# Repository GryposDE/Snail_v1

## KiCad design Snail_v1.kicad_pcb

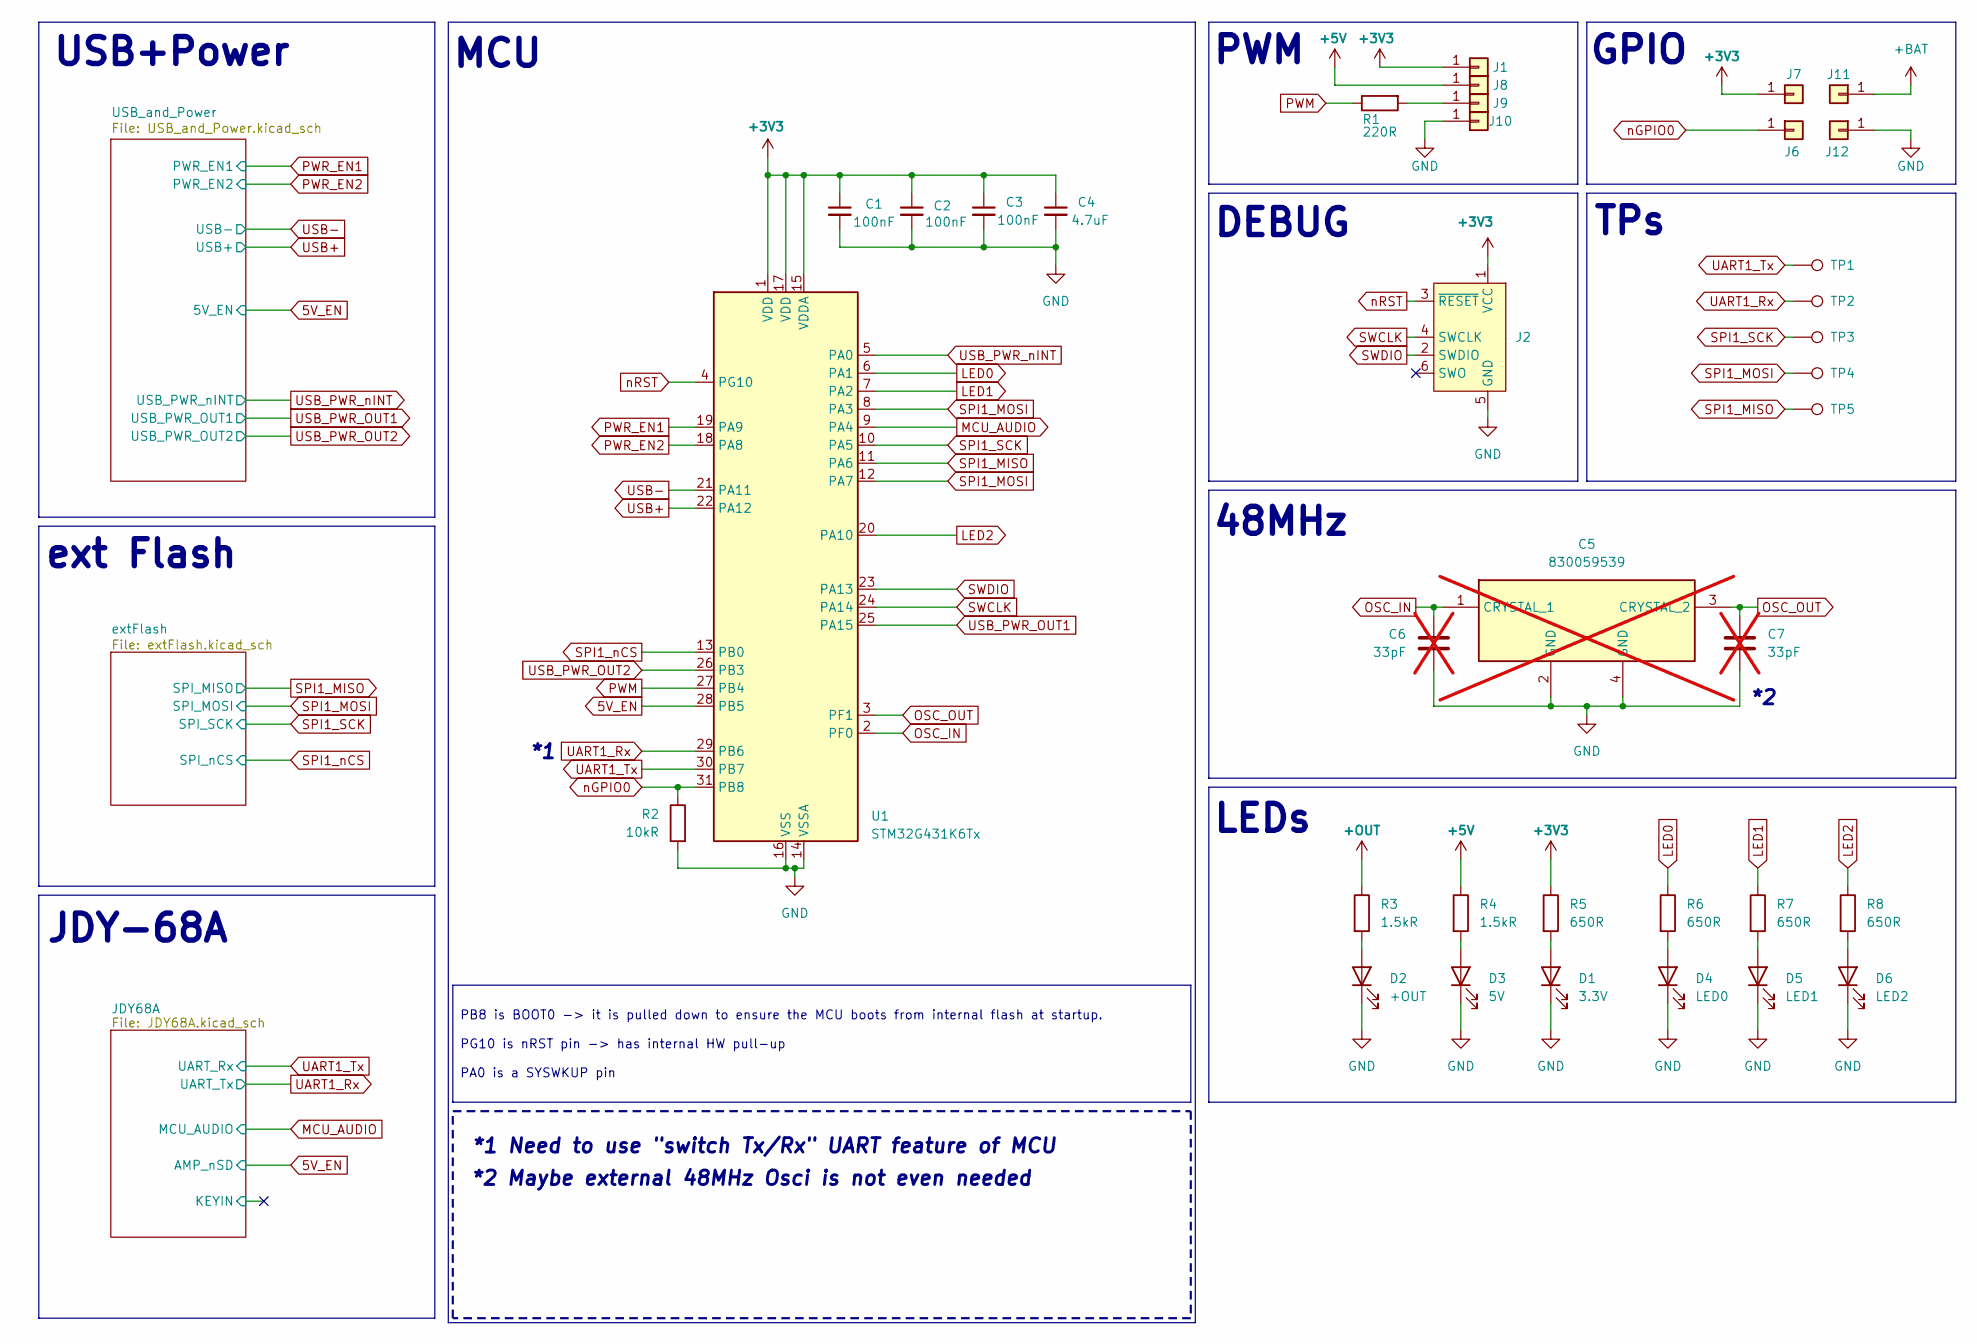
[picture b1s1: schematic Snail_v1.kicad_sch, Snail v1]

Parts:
C1, C2, C3: 100nF; C_0805_2012Metric_Pad1.18x1.45mm_HandSolder
C4: 4.7uF; C_0805_2012Metric_Pad1.18x1.45mm_HandSolder
C5: 830059539; Mouser Part Number 710-830059539; not fitted
C6, C7: 33pF; C_0805_2012Metric_Pad1.18x1.45mm_HandSolder; not fitted
D1: 3.3V; LED_0805_2012Metric_Pad1.15x1.40mm_HandSolder
D2: +OUT; LED_0805_2012Metric_Pad1.15x1.40mm_HandSolder
D3: 5V; LED_0805_2012Metric_Pad1.15x1.40mm_HandSolder
D4: LED0; LED_0805_2012Metric_Pad1.15x1.40mm_HandSolder
D5: LED1; LED_0805_2012Metric_Pad1.15x1.40mm_HandSolder
D6: LED2; LED_0805_2012Metric_Pad1.15x1.40mm_HandSolder
J1, J6, J7, J8, J9, J10, J11, J12: Conn_01x01; SolderWirePad_1x01_SMD_1.5x3mm
J2: Conn_ARM_SWD_TagConnect_TC2030-NL; Tag-Connect_TC2030-IDC-NL_2x03_P1.27mm_Vertical
R1: 220R; R_0805_2012Metric_Pad1.20x1.40mm_HandSolder
R2: 10kR; R_0805_2012Metric_Pad1.20x1.40mm_HandSolder
R3, R4: 1.5kR; R_0805_2012Metric_Pad1.20x1.40mm_HandSolder
R5, R6, R7, R8: 650R; R_0805_2012Metric_Pad1.20x1.40mm_HandSolder
TP1, TP2, TP3, TP4, TP5: TestPoint; TestPoint_Pad_D1.0mm
U1: STM32G431K6Tx; LQFP-32_7x7mm_P0.8mm

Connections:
5V_EN: U1.28 (PB5); also elsewhere on the board
+3V3: C1.1, C2.1, C3.1, C4.1, J1.1, J2.1 (VCC), J7.1, R5.1, U1.1 (VDD), U1.15 (VDDA), U1.17 (VDD); also elsewhere on the board
+5V: J8.1, R4.1; also elsewhere on the board
+OUT: R3.1; also elsewhere on the board
GND: C1.2, C2.2, C3.2, C4.2, C5.2 (GND), C5.4 (GND), C6.2, C7.2, D1.1 (K), D2.1 (K), D3.1 (K), D4.1 (K), D5.1 (K), D6.1 (K), J2.5 (GND), J10.1, J12.1, R2.2, U1.14 (VSSA), U1.16 (VSS), U1.32 (VSS); also elsewhere on the board
LED0: R6.1, U1.6 (PA1)
LED1: R7.1, U1.7 (PA2)
LED2: R8.1, U1.20 (PA10)
MCU_AUDIO: U1.9 (PA4); also elsewhere on the board
unnamed: D1.2 (A), R5.2
unnamed: D2.2 (A), R3.2
unnamed: D3.2 (A), R4.2
unnamed: D4.2 (A), R6.2
unnamed: D5.2 (A), R7.2
unnamed: D6.2 (A), R8.2
unnamed: J9.1, R1.2
OSC_IN: C5.1 (CRYSTAL_1), C6.1, U1.2 (PF0)
OSC_OUT: C5.3 (CRYSTAL_2), C7.1, U1.3 (PF1)
PWM: R1.1, U1.27 (PB4)
PWR_EN1: U1.19 (PA9); also elsewhere on the board
PWR_EN2: U1.18 (PA8); also elsewhere on the board
SPI1_MISO: TP5.1, U1.11 (PA6); also elsewhere on the board
SPI1_MOSI: TP4.1, U1.8 (PA3), U1.12 (PA7); also elsewhere on the board
SPI1_SCK: TP3.1, U1.10 (PA5); also elsewhere on the board
SPI1_nCS: U1.13 (PB0); also elsewhere on the board
SWCLK: J2.4 (SWCLK), U1.24 (PA14)
SWDIO: J2.2 (SWDIO), U1.23 (PA13)
UART1_Rx: TP2.1, U1.29 (PB6); also elsewhere on the board
UART1_Tx: TP1.1, U1.30 (PB7); also elsewhere on the board
USB+: U1.22 (PA12); also elsewhere on the board
USB-: U1.21 (PA11); also elsewhere on the board
USB_PWR_OUT1: U1.25 (PA15); also elsewhere on the board
USB_PWR_OUT2: U1.26 (PB3); also elsewhere on the board
USB_PWR_nINT: U1.5 (PA0); also elsewhere on the board
nGPIO0: J6.1, R2.1, U1.31 (PB8); also elsewhere on the board
nRST: J2.3 (~RESET), U1.4 (PG10)

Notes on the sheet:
*2 Maybe external 48MHz Osci is not even needed
ext Flash
USB+Power
DEBUG
TPs
LEDs
JDY-68A
*1 Need to use "switch Tx/Rx" UART feature of MCU
MCU
PWM
GPIO
48MHz
PB8 is BOOT0 -> it is pulled down to ensure the MCU boots from internal flash at startup. PG10 is nRST pin -> has internal HW pull-up PA0 is a SYSWKUP pin

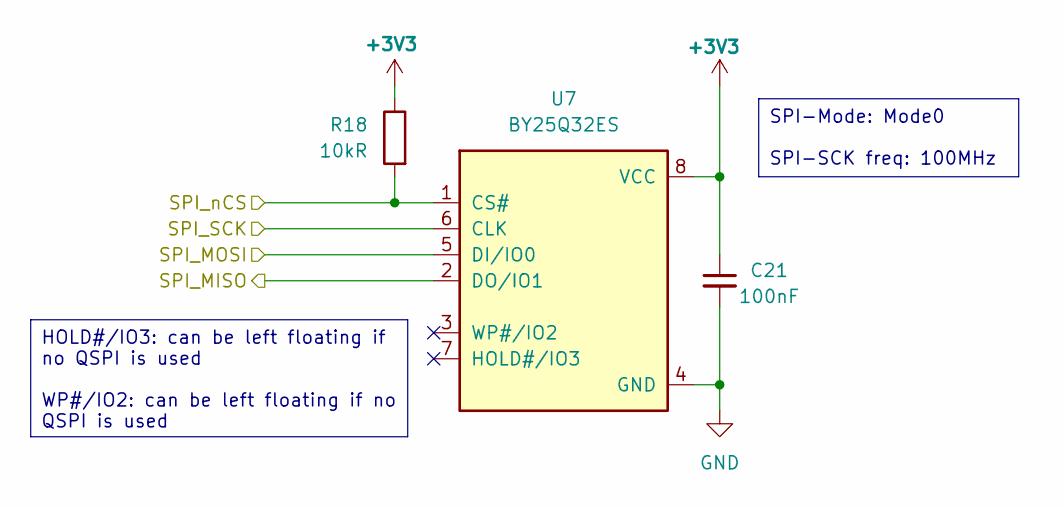
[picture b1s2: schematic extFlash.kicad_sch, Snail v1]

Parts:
C21: 100nF; C_0805_2012Metric_Pad1.18x1.45mm_HandSolder
R18: 10kR; R_0805_2012Metric_Pad1.20x1.40mm_HandSolder
U7: BY25Q32ES; BY25Q32ESSIG_SOIC-8_208mil

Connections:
+3V3: C21.1, R18.1, U7.8 (VCC); also elsewhere on the board
GND: C21.2, U7.4 (GND); also elsewhere on the board
SPI1_MISO: U7.2 (DO/IO1); also elsewhere on the board
SPI1_MOSI: U7.5 (DI/IO0); also elsewhere on the board
SPI1_SCK: U7.6 (CLK); also elsewhere on the board
SPI1_nCS: R18.2, U7.1 (CS#); also elsewhere on the board

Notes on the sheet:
SPI-Mode: Mode0 SPI-SCK freq: 100MHz
HOLD#/IO3: can be left floating if no QSPI is used WP#/IO2: can be left floating if no QSPI is used

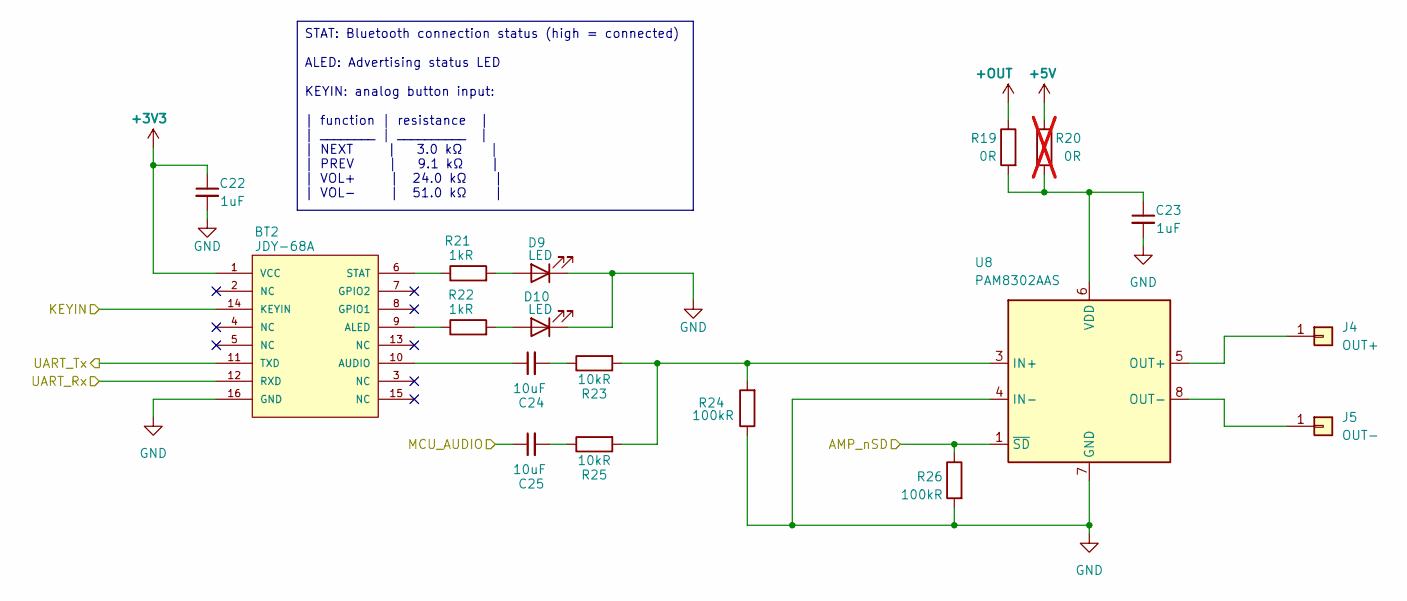
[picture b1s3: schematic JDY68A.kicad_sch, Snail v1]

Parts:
BT2: JDY-68A; JDY-68A_Module
C22, C23: 1uF; C_0805_2012Metric_Pad1.18x1.45mm_HandSolder
C24, C25: 10uF; C_0805_2012Metric_Pad1.18x1.45mm_HandSolder
D9, D10: LED; LED_0805_2012Metric_Pad1.15x1.40mm_HandSolder
J4: OUT+; SolderWirePad_1x01_SMD_1.5x3mm
J5: OUT-; SolderWirePad_1x01_SMD_1.5x3mm
R19: 0R; R_0805_2012Metric_Pad1.20x1.40mm_HandSolder
R20: 0R; R_0805_2012Metric_Pad1.20x1.40mm_HandSolder; not fitted
R21, R22: 1kR; R_0805_2012Metric_Pad1.20x1.40mm_HandSolder
R23, R25: 10kR; R_0805_2012Metric_Pad1.20x1.40mm_HandSolder
R24, R26: 100kR; R_0805_2012Metric_Pad1.20x1.40mm_HandSolder
U8: PAM8302AAS; MSOP-8_3x3mm_P0.65mm

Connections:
5V_EN: R26.1, U8.1 (~SD); also elsewhere on the board
+3V3: BT2.1 (VCC), C22.1; also elsewhere on the board
+5V: R20.1; also elsewhere on the board
+OUT: R19.1; also elsewhere on the board
/JDY68A/KEYIN: BT2.14 (KEYIN)
GND: BT2.16 (GND), C22.2, C23.2, D9.1 (K), D10.1 (K), R24.1, R26.2, U8.4 (IN-), U8.7 (GND); also elsewhere on the board
MCU_AUDIO: C25.1; also elsewhere on the board
unnamed: BT2.9 (ALED), R22.1
unnamed: BT2.10 (AUDIO), C24.1
unnamed: BT2.6 (STAT), R21.1
unnamed: C24.2, R23.1
unnamed: C25.2, R25.1
unnamed: D9.2 (A), R21.2
unnamed: D10.2 (A), R22.2
unnamed: J4.1, U8.5 (OUT+)
unnamed: J5.1, U8.8 (OUT-)
unnamed: R23.2, R24.2, R25.2, U8.3 (IN+)
unnamed: C23.1, R19.2, R20.2, U8.6 (VDD)
UART1_Rx: BT2.11 (TXD); also elsewhere on the board
UART1_Tx: BT2.12 (RXD); also elsewhere on the board

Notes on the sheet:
STAT: Bluetooth connection status (high = connected) ALED: Advertising status LED KEYIN: analog button input: | function | resistance | | ________ | __________ | | NEXT | 3.0 kΩ | | PREV | 9.1 kΩ | | VOL+ | 24.0 kΩ | | VOL− | 51.0 kΩ |

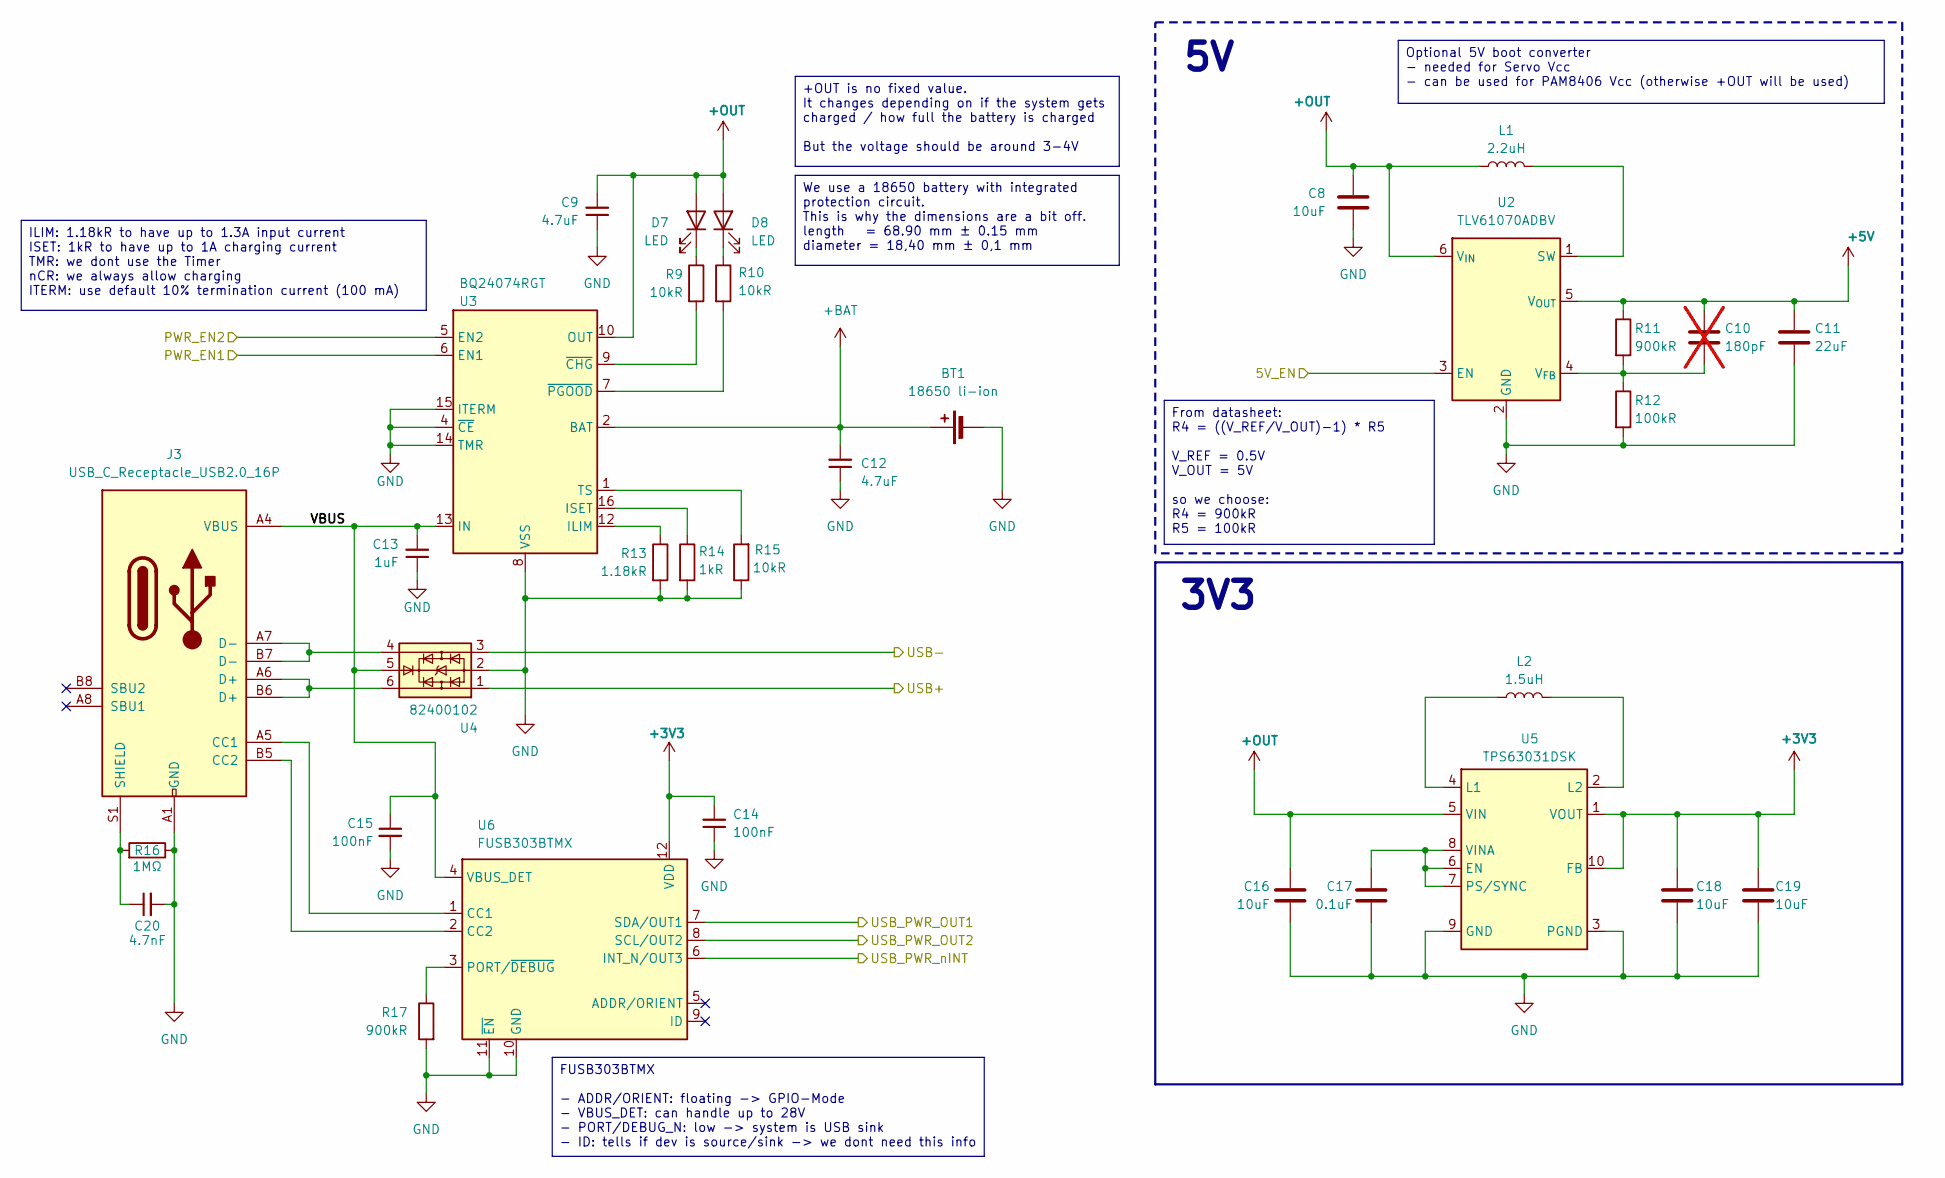
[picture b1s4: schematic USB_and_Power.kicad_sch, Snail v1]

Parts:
BT1: 18650 li-ion; BatteryHolder_MPD_BH-18650-PC
C8, C16, C18, C19: 10uF; C_0805_2012Metric_Pad1.18x1.45mm_HandSolder
C9, C12: 4.7uF; C_0805_2012Metric_Pad1.18x1.45mm_HandSolder
C10: 180pF; C_0805_2012Metric_Pad1.18x1.45mm_HandSolder; not fitted
C11: 22uF; C_0805_2012Metric_Pad1.18x1.45mm_HandSolder
C13: 1uF; C_0805_2012Metric_Pad1.18x1.45mm_HandSolder
C14, C15: 100nF; C_0805_2012Metric_Pad1.18x1.45mm_HandSolder
C17: 0.1uF; C_0805_2012Metric_Pad1.18x1.45mm_HandSolder
C20: 4.7nF; C_0805_2012Metric_Pad1.18x1.45mm_HandSolder
D7, D8: LED; LED_0805_2012Metric_Pad1.15x1.40mm_HandSolder
J3: USB_C_Receptacle_USB2.0_16P; USB_C_Receptacle_GCT_USB4105-xx-A_16P_TopMnt_Horizontal
L1: 2.2uH; L_0805_2012Metric_Pad1.05x1.20mm_HandSolder
L2: 1.5uH; L_0805_2012Metric_Pad1.05x1.20mm_HandSolder
R9, R10, R15: 10kR; R_0805_2012Metric_Pad1.20x1.40mm_HandSolder
R11, R17: 900kR; R_0805_2012Metric_Pad1.20x1.40mm_HandSolder
R12: 100kR; R_0805_2012Metric_Pad1.20x1.40mm_HandSolder
R13: 1.18kR; R_0805_2012Metric_Pad1.20x1.40mm_HandSolder
R14: 1kR; R_0805_2012Metric_Pad1.20x1.40mm_HandSolder
R16: 1MΩ; R_0805_2012Metric_Pad1.20x1.40mm_HandSolder
U2: TLV61070ADBV; SOT95P280X145-6N
U3: BQ24074RGT; VQFN-16-1EP_3x3mm_P0.5mm_EP1.6x1.6mm
U4: 82400102; SOT-23-6
U5: TPS63031DSK; WSON-10-1EP_2.5x2.5mm_P0.5mm_EP1.2x2mm
U6: FUSB303BTMX; Texas_X2QFN-12_1.6x1.6mm_P0.4mm

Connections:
5V_EN: U2.3 (EN); also elsewhere on the board
+3V3: C14.2, C18.1, C19.1, U5.1 (VOUT), U5.10 (FB), U6.12 (VDD); also elsewhere on the board
+5V: C10.1, C11.1, R11.1, U2.5 (V_{OUT}); also elsewhere on the board
+BAT: BT1.1 (+), C12.2, U3.2 (BAT), U3.3 (BAT); also elsewhere on the board
+OUT: C8.1, C9.2, C16.1, D7.2 (A), D8.2 (A), L1.1, U2.6 (V_{IN}), U3.10 (OUT), U3.11 (OUT), U5.5 (VIN); also elsewhere on the board
/USB_and_Power/VBUS: C13.2, C15.1, J3.A4 (VBUS), J3.A9 (VBUS), J3.B4 (VBUS), J3.B9 (VBUS), U3.13 (IN), U4.5, U6.4 (VBUS_DET)
GND: BT1.2 (-), C8.2, C9.1, C11.2, C12.1, C13.1, C14.1, C15.2, C16.2, C17.2, C18.2, C19.2, C20.2, J3.A1 (GND), J3.A12 (GND), J3.B1 (GND), J3.B12 (GND), R12.2, R13.2, R14.2, R15.1, R16.1, R17.2, U2.2 (GND), U3.4 (~CE), U3.8 (VSS), U3.14 (TMR), U3.15 (ITERM), U3.17 (VSS), U4.2, U5.3 (PGND), U5.9 (GND), U6.10 (GND), U6.11 (~EN); also elsewhere on the board
unnamed: D7.1 (K), R9.1
unnamed: D8.1 (K), R10.1
unnamed: J3.A5 (CC1), U6.1 (CC1)
unnamed: J3.B5 (CC2), U6.2 (CC2)
unnamed: J3.A6 (D+), J3.B6 (D+), U4.6
unnamed: J3.A7 (D-), J3.B7 (D-), U4.4
unnamed: C20.1, J3.S1 (SHIELD), R16.2
unnamed: L1.2, U2.1 (SW)
unnamed: C10.2, R11.2, R12.1, U2.4 (V_{FB})
unnamed: R13.1, U3.12 (ILIM)
unnamed: R14.1, U3.16 (ISET)
unnamed: R15.2, U3.1 (TS)
unnamed: R9.2, U3.9 (~CHG)
unnamed: R10.2, U3.7 (~PGOOD)
unnamed: C17.1, U5.6 (EN), U5.7 (PS/SYNC), U5.8 (VINA)
unnamed: L2.1, U5.4 (L1)
unnamed: L2.2, U5.2 (L2)
unnamed: R17.1, U6.3 (PORT/~DEBUG)
PWR_EN1: U3.6 (EN1); also elsewhere on the board
PWR_EN2: U3.5 (EN2); also elsewhere on the board
USB+: U4.1; also elsewhere on the board
USB-: U4.3; also elsewhere on the board
USB_PWR_OUT1: U6.7 (SDA/OUT1); also elsewhere on the board
USB_PWR_OUT2: U6.8 (SCL/OUT2); also elsewhere on the board
USB_PWR_nINT: U6.6 (INT_N/OUT3); also elsewhere on the board

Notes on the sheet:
3V3
ILIM: 1.18kR to have up to 1.3A input current ISET: 1kR to have up to 1A charging current TMR: we dont use the Timer nCR: we always allow charging ITERM: use default 10% termination current (100 mA)
From datasheet: R4 = ((V_REF​/V_OUT)​​−1) * R5 V_REF = 0.5V V_OUT = 5V so we choose: R4 = 900kR R5 = 100kR
FUSB303BTMX - ADDR/ORIENT: floating -> GPIO-Mode - VBUS_DET: can handle up to 28V - PORT/DEBUG_N: low -> system is USB sink - ID: tells if dev is source/sink -> we dont need this info
We use a 18650 battery with integrated protection circuit. This is why the dimensions are a bit off. length = 68.90 mm ± 0.15 mm diameter = 18,40 mm ± 0,1 mm
+OUT is no fixed value. It changes depending on if the system gets charged / how full the battery is charged But the voltage should be around 3-4V
Optional 5V boot converter - needed for Servo Vcc - can be used for PAM8406 Vcc (otherwise +OUT will be used)

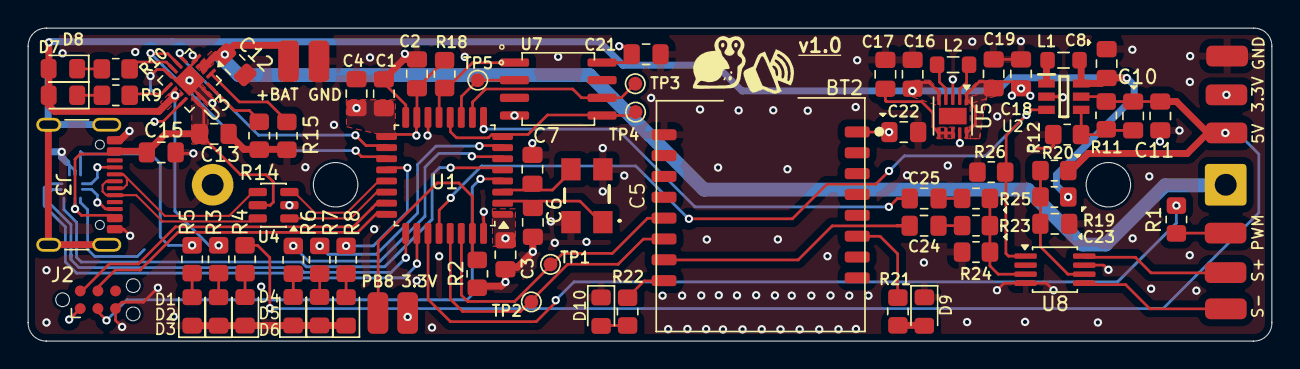
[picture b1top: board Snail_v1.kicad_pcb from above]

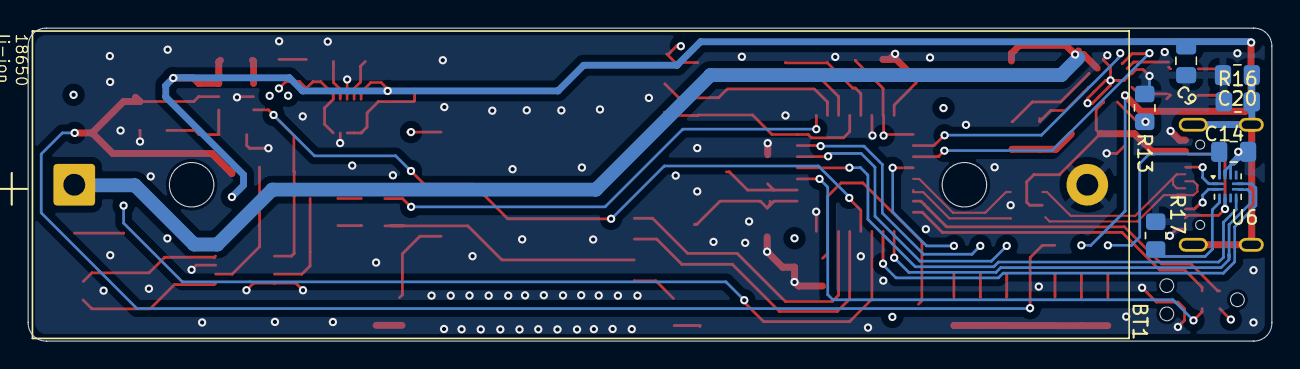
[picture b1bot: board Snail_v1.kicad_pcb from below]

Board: 4 copper layers, 89.5 x 22.5 mm, 90 parts (8 on the bottom side), 67 nets.

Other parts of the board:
3.3V: Conn_01x01; SolderWirePad_1x01_SMD_1.5x3mm
+BAT: Conn_01x01; SolderWirePad_1x01_SMD_1.5x3mm
GND: Conn_01x01; SolderWirePad_1x01_SMD_1.5x3mm
PB8: Conn_01x01; SolderWirePad_1x01_SMD_1.5x3mm

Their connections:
+3V3: 3.3V.1; also elsewhere on the board
+BAT: +BAT.1; also elsewhere on the board
GND: GND.1; also elsewhere on the board
nGPIO0: PB8.1; also elsewhere on the board

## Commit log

2026-03-28 Added USB+Power circuit
2026-03-29 Added 5V, 3V3, PAM circuit
2026-04-04 Added BY25Q32 extFlash
2026-04-04 Added JDY-68A and replaced Amp-IC for PAM8302AAS
2026-04-04 Changed LDO to Buc-Boost
2026-04-04 Added LEDs + TPs
2026-04-04 Added missing footprints
2026-04-04 Started with layout
2026-04-05 Added layout
2026-04-06 Did Silkscreen + added images of PCBA
2026-04-06 Added missing AMP_nSD connection to MCU via 5V_EN
2026-04-06 Added rounded corners to PCB
2026-04-08 Changed layout + added dimensions
2026-04-18 Added +BAT and GND Pad to design
